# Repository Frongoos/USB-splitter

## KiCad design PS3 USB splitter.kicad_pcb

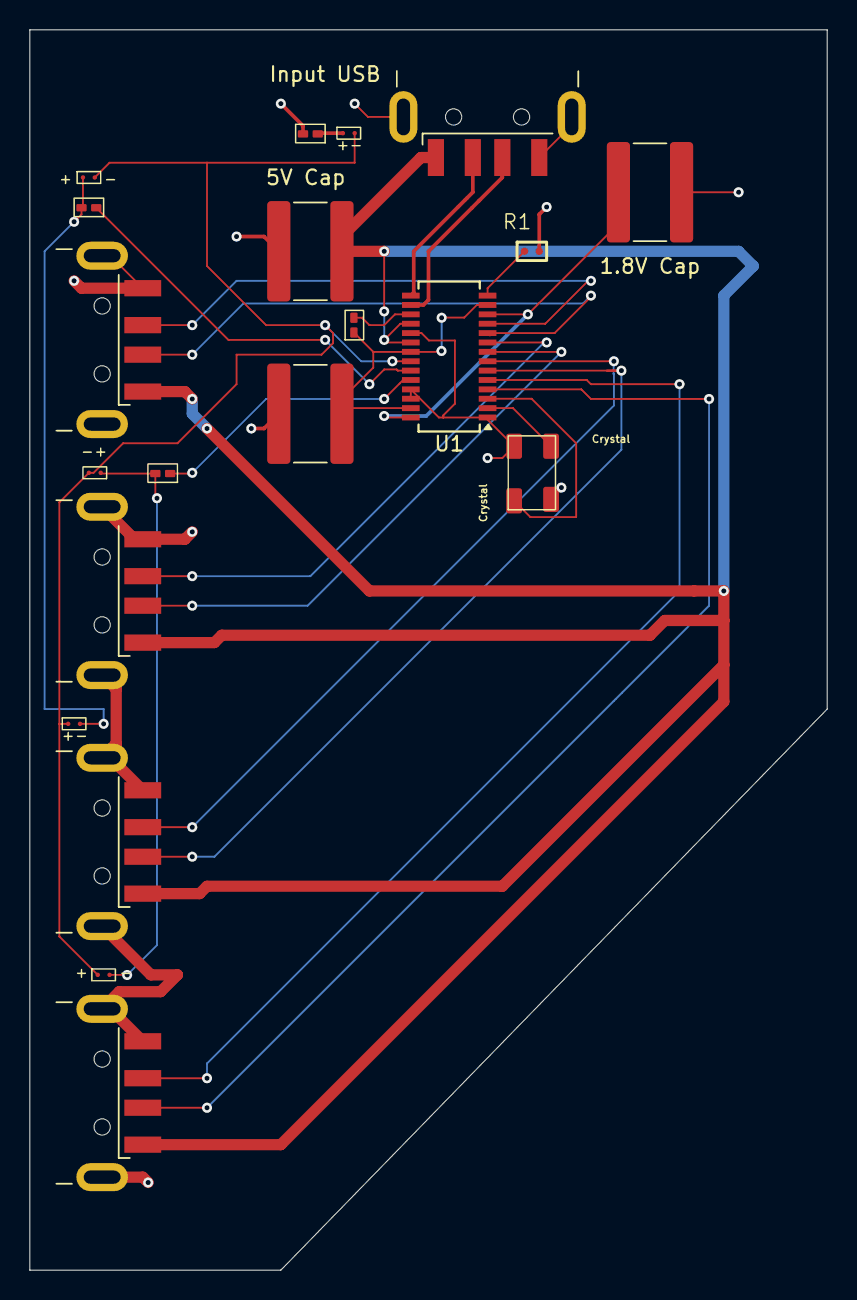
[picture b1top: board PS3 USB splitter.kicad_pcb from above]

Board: 4 copper layers, 54.0 x 84.0 mm, 20 parts (0 on the bottom side), 24 nets.

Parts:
1.8V Cap, 3.3decoup1, 5V Cap: 10uF; C_1825_4564Metric_Pad1.57x6.80mm_HandSolder
AMDcrystal1: Crystal
Input USB: USB_A; USB_A_CNCTech_1001-011-01101_Horizontal
Port1, Port2, Port3, Port4: USB_A; USB_A_CNCTech_1001-011-01101_Horizontal
Port1Ind1: Port1LED; LWD
Port2ind1: Port2LED; LWD
Port3ind1: POrt3LED; LWD
Port4ind1: Port4LED; LWD
R1: 2700; 2.7k Resistor
R2: LED1and3resistor; 10k resistor
R3: LEd2and4resistor; 10k resistor
R5: 10K; 10k resistor
REDLED1: Power LED; LWD
U1: FE1.1s; SSOP-28_3.9x9.9mm_P0.635mm
XRSTJpullup1: 10K; 10k resistor

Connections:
1:D+: Port1.3 (D+), U1.11 (DP1)
1:D-: Port1.2 (D-), U1.10 (DM1)
2:D+: Port2.3 (D+), U1.9 (DP2)
2:D-: Port2.2 (D-), U1.8 (DM2)
3:D+: Port3.3 (D+), U1.7 (DP3)
3:D-: Port3.2 (D-), U1.6 (DM3)
4:D+: Port4.3 (D+), U1.5 (DP4)
4:D-: Port4.2 (D-), U1.4 (DM4)
/3.3V: 3.3decoup1.2, U1.13 (VD33), U1.21 (VD33_O), U1.27 (TESTJ/EESDA), XRSTJpullup1.1
GND: 1.8V Cap.1, 3.3decoup1.1, 5V Cap.2, AMDcrystal1.2 (GND), AMDcrystal1.4 (GND), Input USB.4 (GND), Input USB.5 (Shield), Port1.4 (GND), Port1.5 (Shield), Port2.4 (GND), Port2.5 (Shield), Port3.4 (GND), Port3.5 (Shield), Port4.4 (GND), Port4.5 (Shield), R1.2, R5.2, U1.1 (VSS), U1.19 (BUSJ), U1.25 (PWRJ), U1.26 (OVCJ)
unnamed: AMDcrystal1.1 (XIN), U1.3 (XIN)
unnamed: AMDcrystal1.3 (XOUT), U1.2 (XOUT)
unnamed: Input USB.3 (D+), U1.16 (DPU)
unnamed: Input USB.2 (D-), U1.15 (DMU)
unnamed: Port1Ind1.2 (A), Port2ind1.2 (A), Port3ind1.1 (K), Port4ind1.1 (K), REDLED1.2 (A), U1.22 (DRV)
unnamed: Port1Ind1.1 (K), Port3ind1.2 (A), R2.2
unnamed: Port2ind1.1 (K), Port4ind1.2 (A), R3.2
unnamed: R5.1, REDLED1.1 (K)
unnamed: R2.1, U1.23 (LED1/EESCL)
unnamed: R3.1, U1.24 (LED2)
unnamed: R1.1, U1.14 (REXT)
unnamed: 1.8V Cap.2, U1.12 (VD18_O), U1.28 (VD18)
unnamed: U1.17 (~XRSTJ), XRSTJpullup1.2
vbus power: 5V Cap.1, Input USB.1 (VBUS), Port1.1 (VBUS), Port2.1 (VBUS), Port3.1 (VBUS), Port4.1 (VBUS), U1.18 (VBUSM), U1.20 (VDD5)
